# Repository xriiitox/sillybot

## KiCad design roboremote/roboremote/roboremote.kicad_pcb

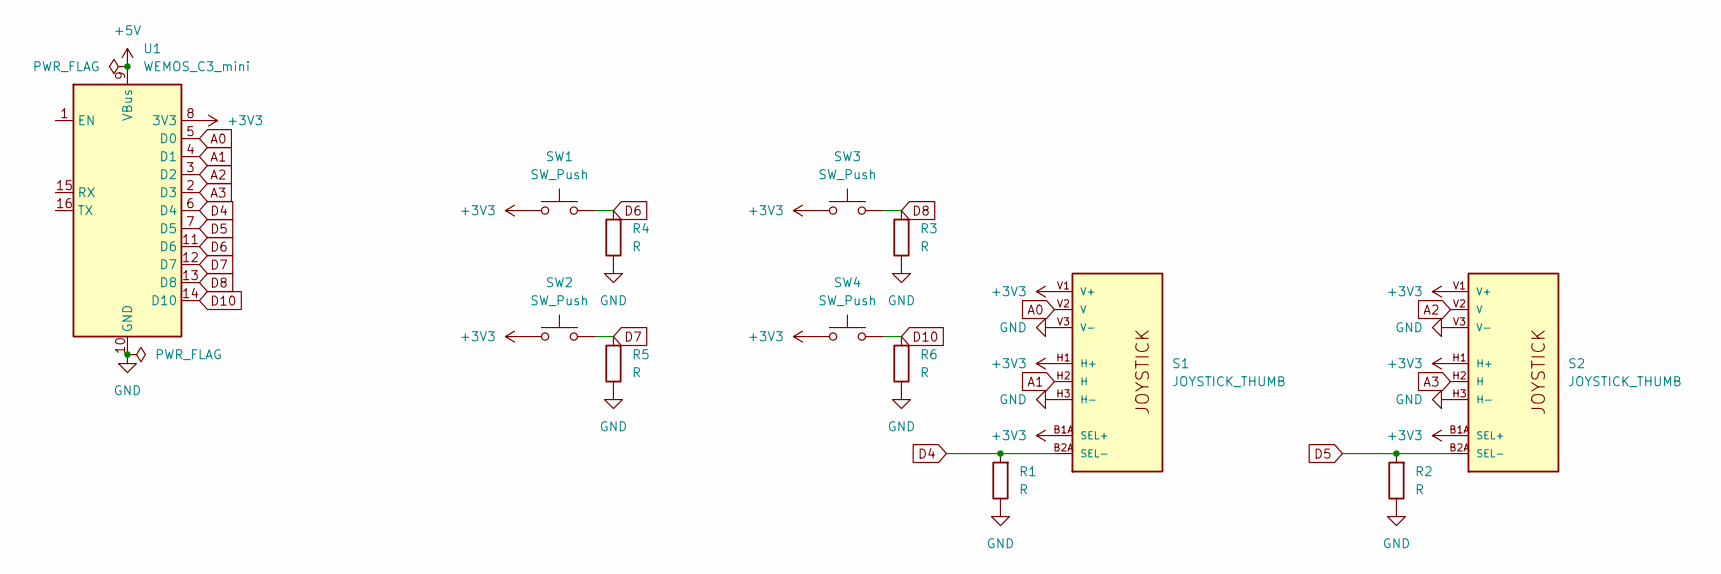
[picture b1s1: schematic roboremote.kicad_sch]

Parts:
R1, R2, R3, R4, R5, R6: R; R_Axial_DIN0207_L6.3mm_D2.5mm_P10.16mm_Horizontal
S1, S2: JOYSTICK_THUMB; JOYSTICK
SW1, SW2, SW3, SW4: SW_Push; MX-Solderable-1U
U1: WEMOS_C3_mini

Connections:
+3V3: S1.B1A (SEL+), S1.H1 (H+), S1.V1 (V+), S2.B1A (SEL+), S2.H1 (H+), S2.V1 (V+), SW1.1, SW2.1, SW3.1, SW4.1, U1.8 (3V3)
+5V: U1.9 (VBus)
A0: S1.V2 (V), U1.5 (D0)
A1: S1.H2 (H), U1.4 (D1)
A2: S2.V2 (V), U1.3 (D2)
A3: S2.H2 (H), U1.2 (D3)
D4: R1.2, S1.B2A (SEL-), U1.6 (D4)
D5: R2.2, S2.B2A (SEL-), U1.7 (D5)
D6: R4.2, SW1.2, U1.11 (D6)
D7: R5.2, SW2.2, U1.12 (D7)
D8: R3.2, SW3.2, U1.13 (D8)
D10: R6.2, SW4.2, U1.14 (D10)
GND: R1.1, R2.1, R3.1, R4.1, R5.1, R6.1, S1.H3 (H-), S1.V3 (V-), S2.H3 (H-), S2.V3 (V-), U1.10 (GND)

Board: 2 copper layers, 13 parts (0 on the bottom side), 12 nets, no tracks yet.

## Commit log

2025-05-22 pcb schematic and design beginnings
2025-05-22 pcb components layout and start journal
